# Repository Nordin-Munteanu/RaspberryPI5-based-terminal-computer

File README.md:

# RaspberryPI5-based-terminal-computer
A raspberry pi 5 based computer using a monochrome CRT display

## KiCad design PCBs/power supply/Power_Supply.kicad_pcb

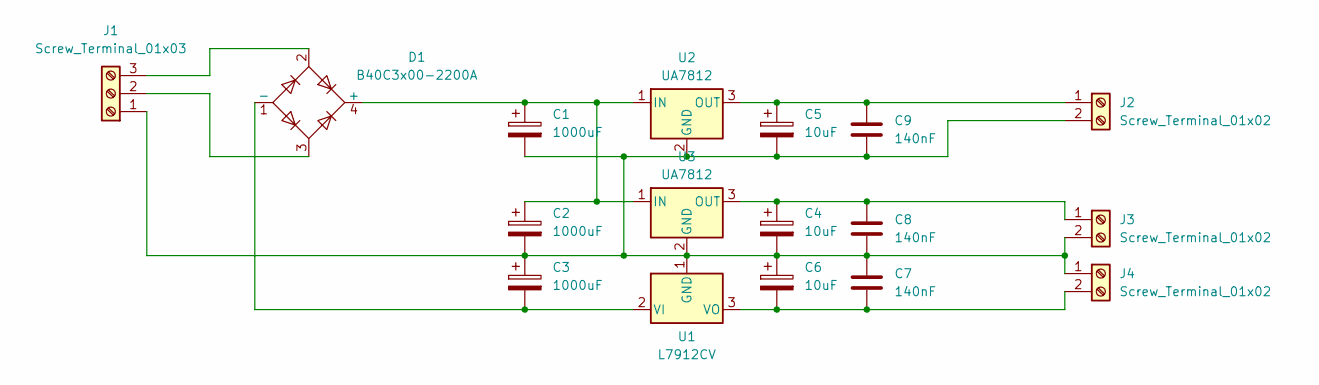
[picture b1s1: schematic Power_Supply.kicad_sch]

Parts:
C1, C2, C3: 1000uF; CP_Radial_D16.0mm_P7.50mm
C4, C5, C6: 10uF; CP_Radial_D5.0mm_P2.00mm
C7, C8, C9: 140nF; C_Rect_L7.0mm_W4.5mm_P5.00mm
D1: B40C3x00-2200A; Diode_Bridge_19.0x3.5x10.0mm_P5.0mm
J1: Screw_Terminal_01x03; TerminalBlock_Phoenix_PT-1,5-3-5.0-H_1x03_P5.00mm_Horizontal
J2, J3, J4: Screw_Terminal_01x02; TerminalBlock_Phoenix_MKDS-1,5-2_1x02_P5.00mm_Horizontal
U1: L7912CV; TO-220-3_Vertical
U2, U3: UA7812; TO-220-3_Vertical

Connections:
unnamed: C1.1, C2.1, D1.4 (+), U2.1 (IN), U3.1 (IN)
unnamed: C3.2, D1.1 (-), U1.2 (VI)
unnamed: C1.2, C2.2, C3.1, C4.2, C5.2, C6.1, C7.1, C8.2, C9.2, J1.1, J2.2, J3.2, J4.1, U1.1 (GND), U2.2 (GND), U3.2 (GND)
unnamed: D1.3, J1.2
unnamed: D1.2, J1.3
unnamed: C5.1, C9.1, J2.1, U2.3 (OUT)
unnamed: C4.1, C8.1, J3.1, U3.3 (OUT)
unnamed: C6.2, C7.2, J4.2, U1.3 (VO)

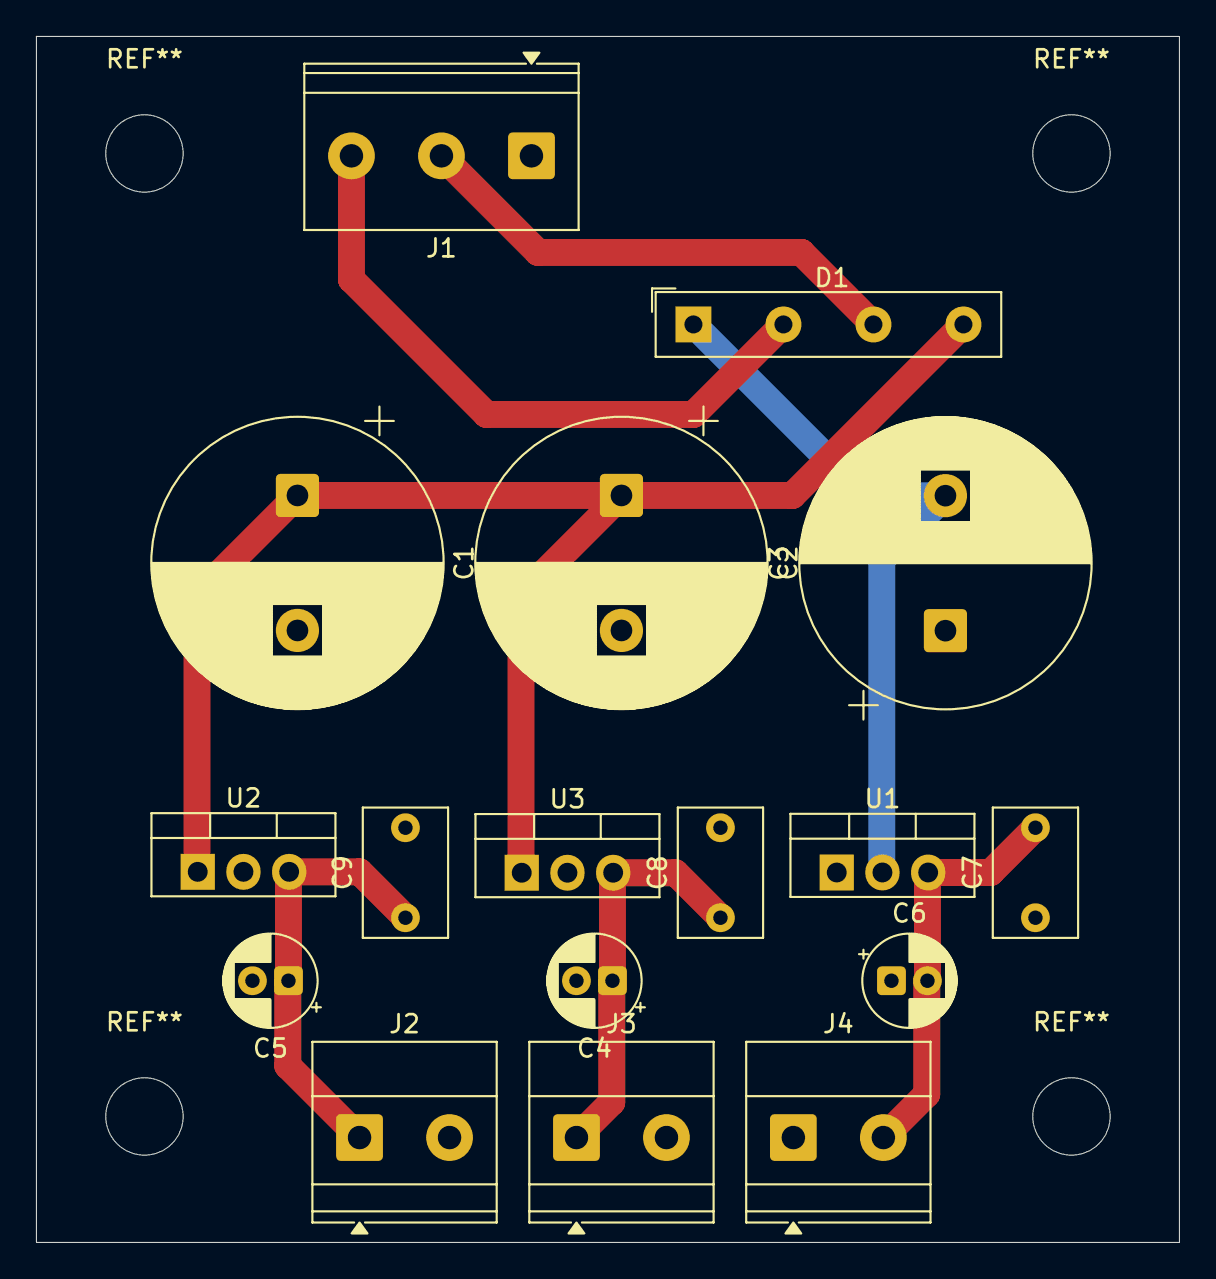
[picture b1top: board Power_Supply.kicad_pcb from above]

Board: 2 copper layers, 63.5 x 67.0 mm, 17 parts (0 on the bottom side), 8 nets.

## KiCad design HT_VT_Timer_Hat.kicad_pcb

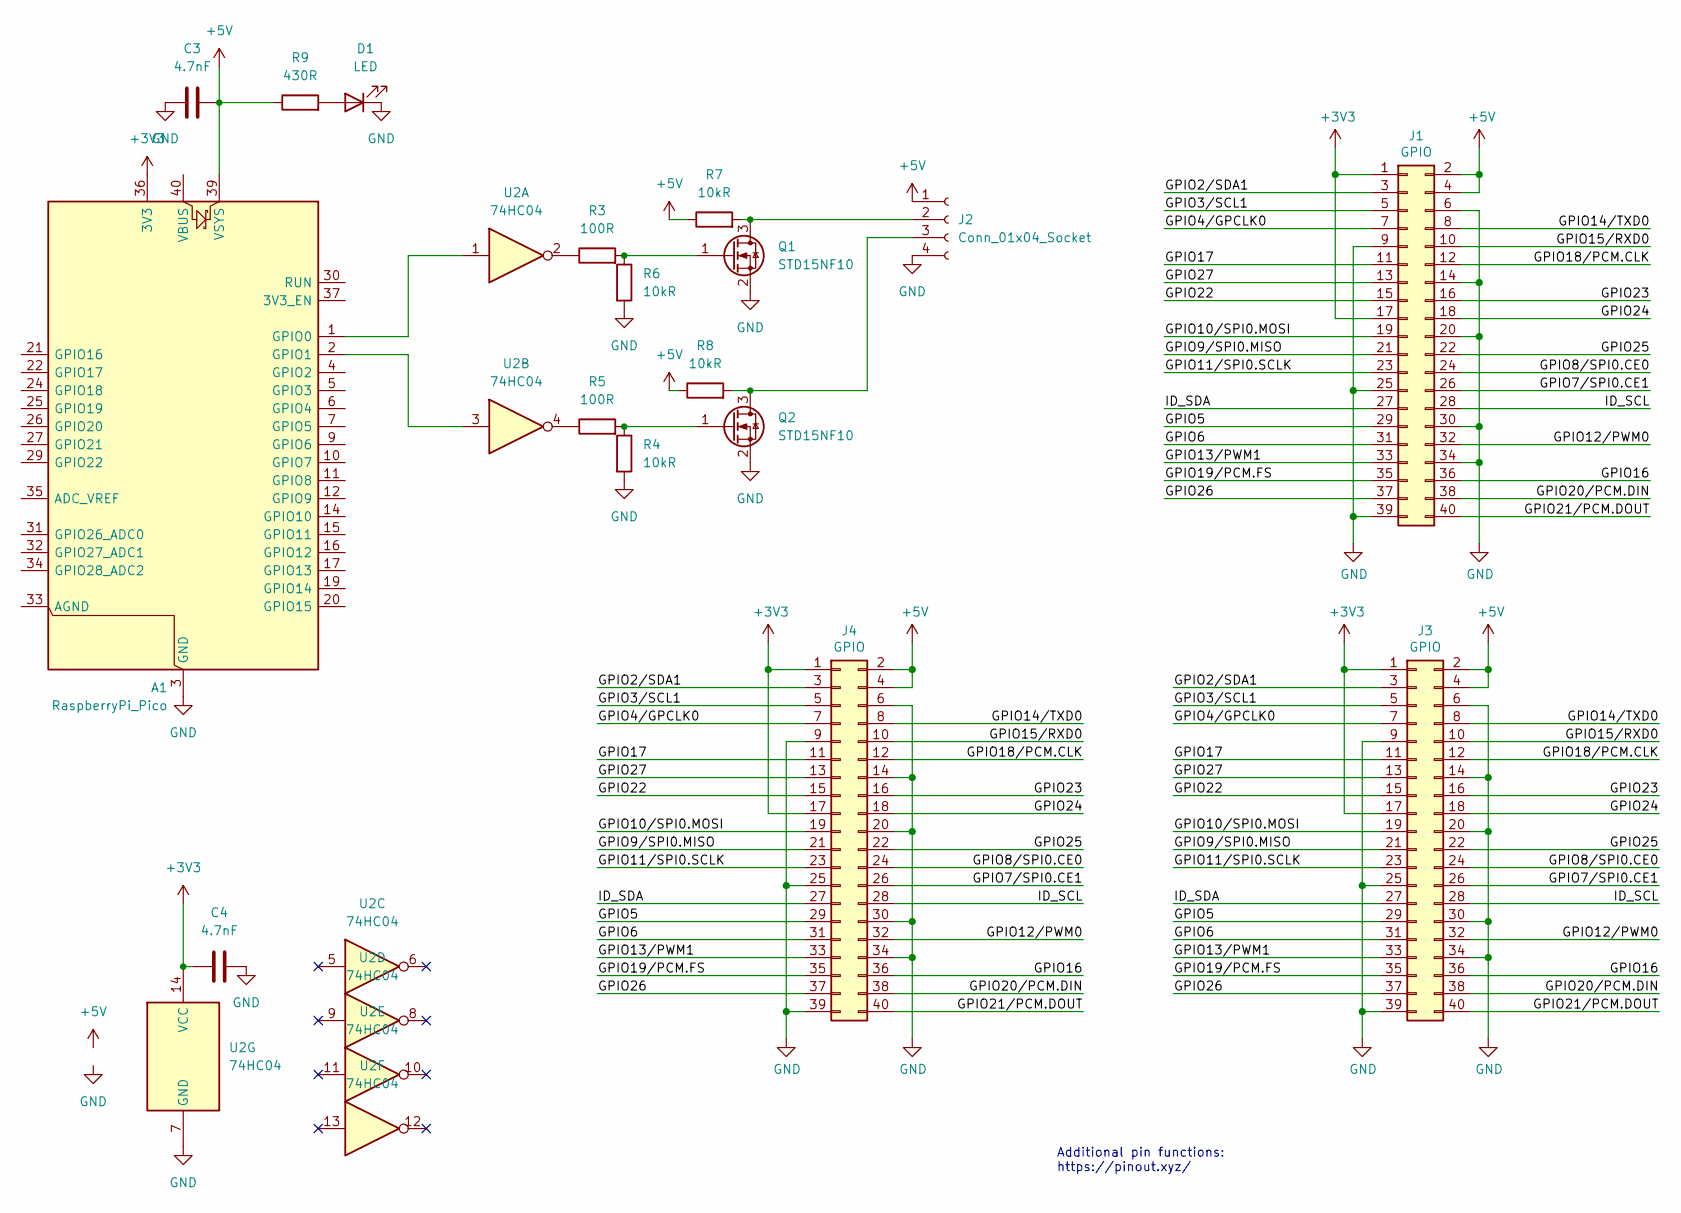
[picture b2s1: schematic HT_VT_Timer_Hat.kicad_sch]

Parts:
A1: RaspberryPi_Pico; RaspberryPi_Pico_Common_Unspecified
C3, C4: 4.7nF; C_0805_2012Metric
D1: LED; LED_0805_2012Metric
J1, J4: GPIO; PinSocket_2x20_P2.54mm_Vertical
J2: Conn_01x04_Socket; JST_ACH_BM04B-ACHSS-A-GAN-ETF_1x04-1MP_P1.20mm_Vertical
J3: GPIO; PinHeader_2x20_P2.54mm_Vertical
Q1, Q2: STD15NF10; TO-252-2
R3, R5: 100R; R_Axial_DIN0204_L3.6mm_D1.6mm_P1.90mm_Vertical
R4, R6, R7, R8: 10kR; R_Axial_DIN0204_L3.6mm_D1.6mm_P1.90mm_Vertical
R9: 430R; R_Axial_DIN0204_L3.6mm_D1.6mm_P1.90mm_Vertical
U2: 74HC04; DIP-14_W10.16mm

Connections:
+3V3: A1.36 (3V3), C4.1, J1.1, J1.17, J3.1, J3.17, J4.1, J4.17, U2.14 (VCC)
+5V: A1.39 (VSYS), C3.2, J1.2, J1.4, J2.1, J3.2, J3.4, J4.2, J4.4, R7.1, R8.1, R9.1
/GPIO2/SDA1: J1.3, J3.3, J4.3
/GPIO3/SCL1: J1.5, J3.5, J4.5
/GPIO4/GPCLK0: J1.7, J3.7, J4.7
/GPIO5: J1.29, J3.29, J4.29
/GPIO6: J1.31, J3.31, J4.31
/GPIO7/SPI0.CE1: J1.26, J3.26, J4.26
/GPIO8/SPI0.CE0: J1.24, J3.24, J4.24
/GPIO9/SPI0.MISO: J1.21, J3.21, J4.21
/GPIO10/SPI0.MOSI: J1.19, J3.19, J4.19
/GPIO11/SPI0.SCLK: J1.23, J3.23, J4.23
/GPIO12/PWM0: J1.32, J3.32, J4.32
/GPIO13/PWM1: J1.33, J3.33, J4.33
/GPIO14/TXD0: J1.8, J3.8, J4.8
/GPIO15/RXD0: J1.10, J3.10, J4.10
/GPIO16: J1.36, J3.36, J4.36
/GPIO17: J1.11, J3.11, J4.11
/GPIO18/PCM.CLK: J1.12, J3.12, J4.12
/GPIO19/PCM.FS: J1.35, J3.35, J4.35
/GPIO20/PCM.DIN: J1.38, J3.38, J4.38
/GPIO21/PCM.DOUT: J1.40, J3.40, J4.40
/GPIO22: J1.15, J3.15, J4.15
/GPIO23: J1.16, J3.16, J4.16
/GPIO24: J1.18, J3.18, J4.18
/GPIO25: J1.22, J3.22, J4.22
/GPIO26: J1.37, J3.37, J4.37
/GPIO27: J1.13, J3.13, J4.13
/ID_SCL: J1.28, J3.28, J4.28
/ID_SDA: J1.27, J3.27, J4.27
GND: A1.3 (GND), A1.8 (GND), A1.13 (GND), A1.18 (GND), A1.23 (GND), A1.28 (GND), A1.38 (GND), C3.1, C4.2, D1.1 (K), J1.6, J1.9, J1.14, J1.20, J1.25, J1.30, J1.34, J1.39, J2.4, J3.6, J3.9, J3.14, J3.20, J3.25, J3.30, J3.34, J3.39, J4.6, J4.9, J4.14, J4.20, J4.25, J4.30, J4.34, J4.39, Q1.2 (S), Q2.2 (S), R4.2, R6.2, U2.7 (GND)
unnamed: A1.1 (GPIO0), U2.1
unnamed: A1.2 (GPIO1), U2.3
unnamed: D1.2 (A), R9.2
unnamed: J2.2, Q1.3 (D), R7.2
unnamed: J2.3, Q2.3 (D), R8.2
unnamed: Q1.1 (G), R3.2, R6.1
unnamed: Q2.1 (G), R4.1, R5.2
unnamed: R3.1, U2.2
unnamed: R5.1, U2.4

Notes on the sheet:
Additional pin functions: https://pinout.xyz/

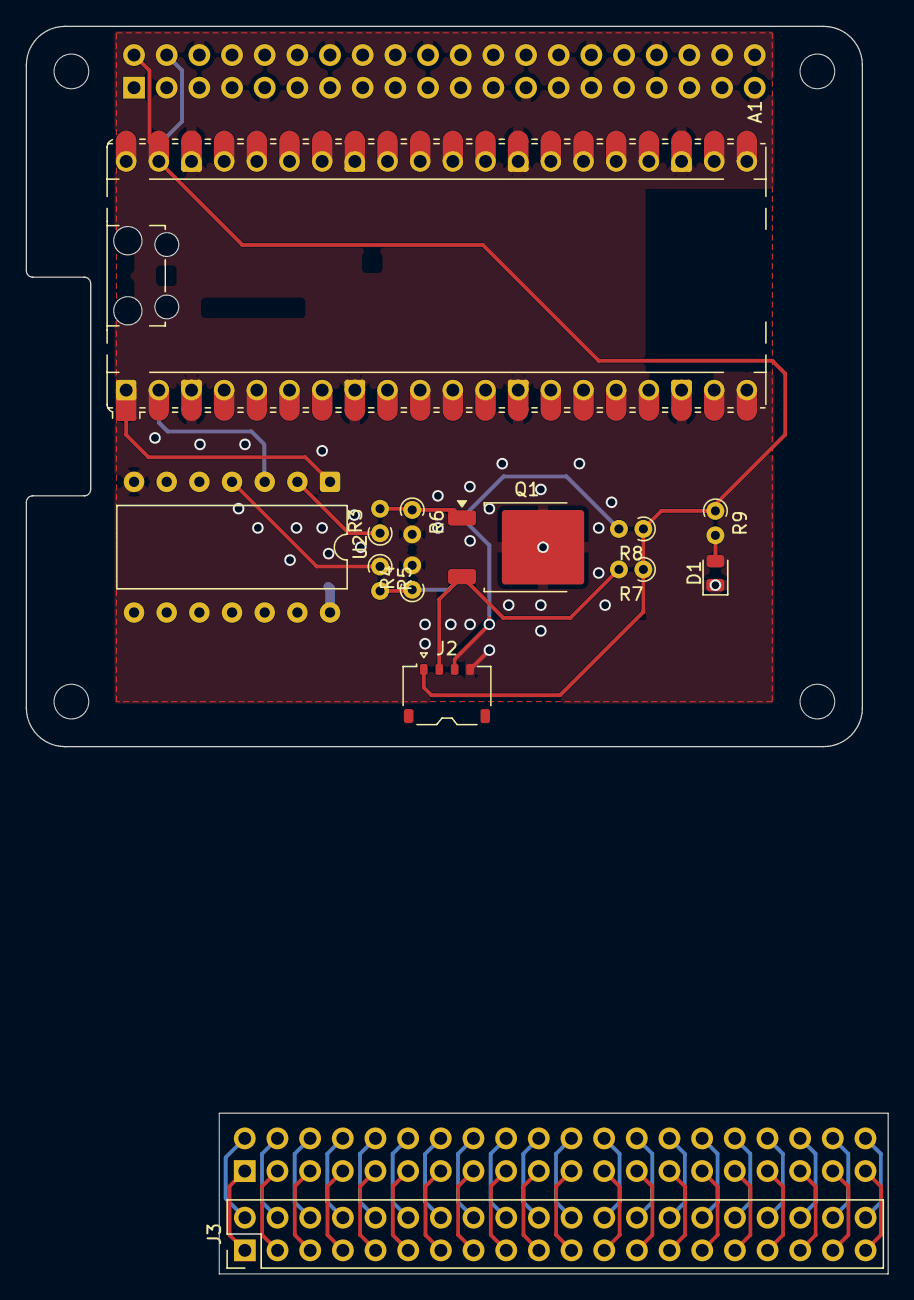
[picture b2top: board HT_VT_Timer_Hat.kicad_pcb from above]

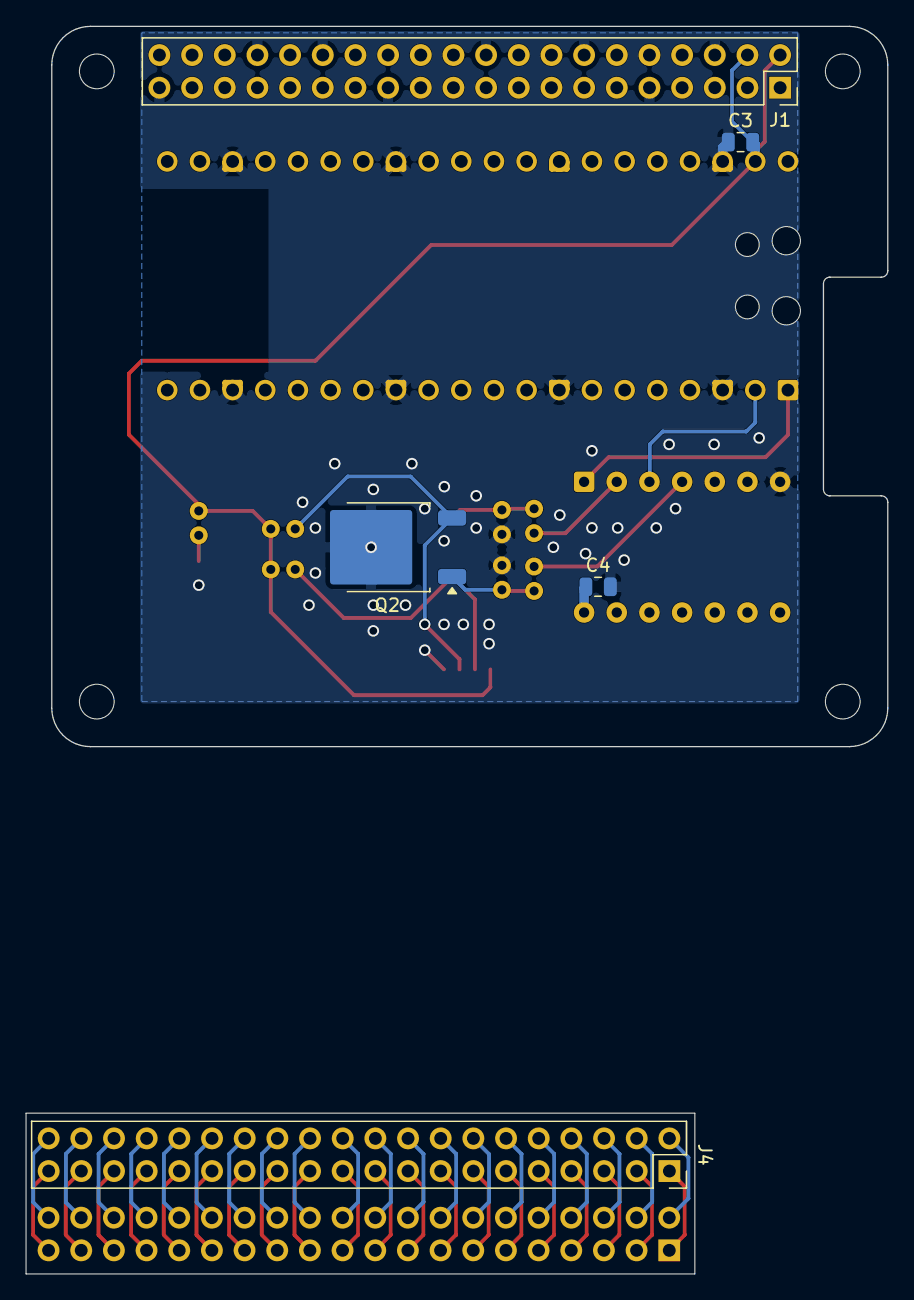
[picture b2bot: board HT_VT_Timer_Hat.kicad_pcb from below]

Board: 2 copper layers, 65.0 x 56.0 mm, 22 parts (5 on the bottom side), 40 nets.

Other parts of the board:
MH1, MH2, MH3, MH4: MountingHole_2.7mm_M2.5
